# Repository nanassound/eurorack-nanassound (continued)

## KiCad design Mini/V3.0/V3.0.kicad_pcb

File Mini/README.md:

# Mini: USB-C Power Supply

A small and portable USB-C power supply for Eurorack modules.

- It takes 5V input from USB-C port and outputs dual supply +/- 12V and 5V.
- The main component that converts the voltage is [Mean Well DKM10E-12](https://www.meanwell-web.com/en-gb/dc-dc-converter-pcb-mount-input-4-7-9vdc-dual-dkm10e--12).
- The output current according to DKM10E-12 datasheet is ±0 ~ 416mA.
- The input voltage range is 4.7V ~ 9V.

## Design decisions and changes log

#### Version 3

- Make the PCB dimension smaller. There's no point to mount it on the rail and wasting hit point.
- Reduce the amount of power header to 2 headers only.
- Add some capacitors to avoid noise.
- Add a switch to on/off the power supply without unplugging the cable.

#### Version 2

- Make the PCB dimension to fit 3U height and 6HP width, so it can be mounted on a 3U rack.
- Replace 10 pin power header with 16 pin power header and pass 5V from USB-C to the module.
- Replace the glass fuse with 4A PPTC (resettable fuse) to protect the circuit from over current.
- Use SMT components as much as possible to make the layout cleaner.

#### Version 1

- To allow Mini to use 10 pin power header and keep the design small, it **does not** pass 5V. If the Eurorack module requires 5V, then it's the responsibility of the module to provide it by converting the voltage.
- I add 4A fuse as a safety measure.

## Tested USB-C sources

- MacBook Pro [70W USB-C power adapter](https://www.apple.com/shop/product/MXN53AM/A)
- MacBook Pro M2 USB-C port.
- 40W USB-C phone charger (I don't know the brand)
- Xiaomi 10000mAh USB-A to USB-C power bank

## Tested Eurorack modules

- Nanas Sound Uksed
- Doepfer A-111-6
- Crea8audio Function Junction

## Where to buy Mini?

If you are in Europe, you can buy the fully assembled Mini 2.0 from my store on [Reverb](https://reverb.com/en-ee/item/92160894-nanas-sound-mini-usb-c-power-supply).

For the customer outside of Europe, you can buy it from a shared project on [PCBWay](https://www.pcbway.com/project/shareproject/Mini_Eurorack_modular_synth_USB_C_power_supply_29aeece2.html) or [Elecrow](https://www.elecrow.com/sharepj/mini-eurorack-modular-synth-usb-c-power-supply-988.html).

## Photos from the test of Mini version 1

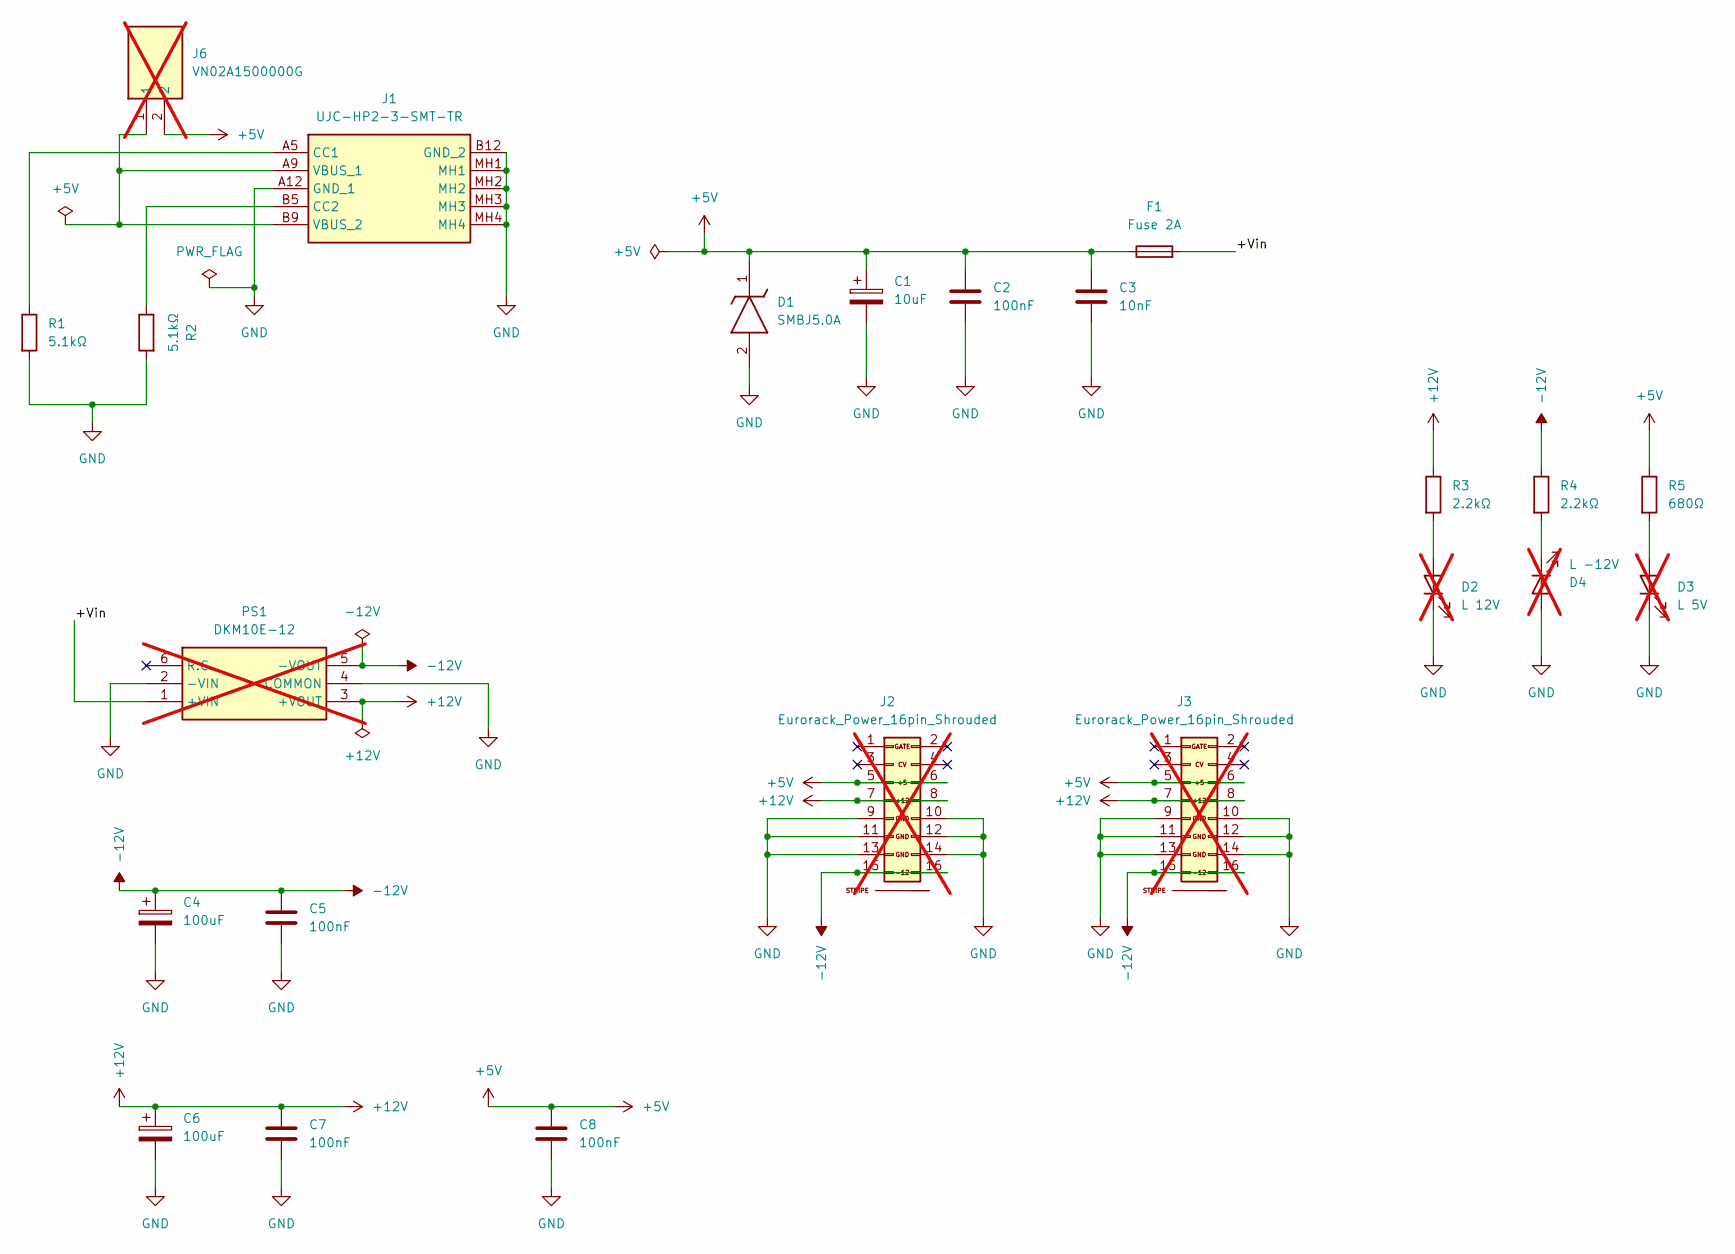
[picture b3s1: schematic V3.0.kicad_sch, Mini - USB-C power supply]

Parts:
C1: 10uF; CP_Elec_6.3x7.7; LCSC Part Number C72482
C2, C5, C7, C8: 100nF; C_0603_1608Metric; LCSC Part Number C14663
C3: 10nF; C_0603_1608Metric; LCSC Part Number C100042
C4, C6: 100uF; CP_Elec_6.3x7.7; LCSC Part Number C48587228
D1: SMBJ5.0A; DIOM5436X244N; Mouser Part Number 652-SMBJ5.0A
D2: L 12V; LED_D2.0mm_W4.8mm_H2.5mm_FlatTop; LCSC Part Number C6717903; not fitted
D3: L 5V; LED_D2.0mm_W4.8mm_H2.5mm_FlatTop; LCSC Part Number C6717903; not fitted
D4: L -12V; LED_D2.0mm_W4.8mm_H2.5mm_FlatTop; LCSC Part Number C6717903; not fitted
F1: Fuse 2A; Fuse_1812_4532Metric; LCSC Part Number C135364
J1: UJC-HP2-3-SMT-TR; UJCHP23SMTTR; Mouser Part Number 179-UJC-HP2-3-SMT-TR
J2, J3: Eurorack_Power_16pin_Shrouded; Pins_2x08_2.54mm_TH_EuroPower_Shrouded_reducedsilk; Part Number LL1007-1 (2*8 HITEMP); not fitted
J6: VN02A1500000G; Mouser Part Number 649-VN02A15000J0G; not fitted
PS1: DKM10E-12; DKM10E12; Mouser Part Number 709-DKM10E-12; not fitted
R1, R2: 5.1kΩ; R_1206_3216Metric; LCSC Part Number C26033
R3, R4: 2.2kΩ; R_1206_3216Metric; LCSC Part Number C17948
R5: 680Ω; R_1206_3216Metric; LCSC Part Number C17975

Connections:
+5V: C1.1, C2.1, C3.1, C8.1, D1.1 (K), F1.1, J2.5 (+12V), J2.6, J3.5 (+12V), J3.6, J6.2, R5.1
+12V: C6.1, C7.1, J2.7 (12V), J2.8 (+12V), J3.7 (12V), J3.8 (+12V), PS1.3 (+VOUT), R3.1
-12V: C4.1, C5.1, J2.15 (-12V), J2.16, J3.15 (-12V), J3.16, PS1.5 (-VOUT), R4.1
/+Vin: F1.2, PS1.1 (+VIN)
GND: C1.2, C2.2, C3.2, C4.2, C5.2, C6.2, C7.2, C8.2, D1.2 (A), D2.1 (K), D3.1 (K), D4.2 (A), J1.A12 (GND_1), J1.B12 (GND_2), J1.MH1, J1.MH2, J1.MH3, J1.MH4, J2.9 (GND), J2.10 (GND), J2.11 (GND), J2.12 (GND), J2.13 (-12), J2.14 (-12V), J3.9 (GND), J3.10 (GND), J3.11 (GND), J3.12 (GND), J3.13 (-12), J3.14 (-12V), PS1.2 (-VIN), PS1.4 (COMMON), R1.2, R2.2
unnamed: D2.2 (A), R3.2
unnamed: D3.2 (A), R5.2
unnamed: D4.1 (K), R4.2
unnamed: J1.A5 (CC1), R1.1
unnamed: J1.B5 (CC2), R2.1
unnamed: J1.A9 (VBUS_1), J1.B9 (VBUS_2), J6.1

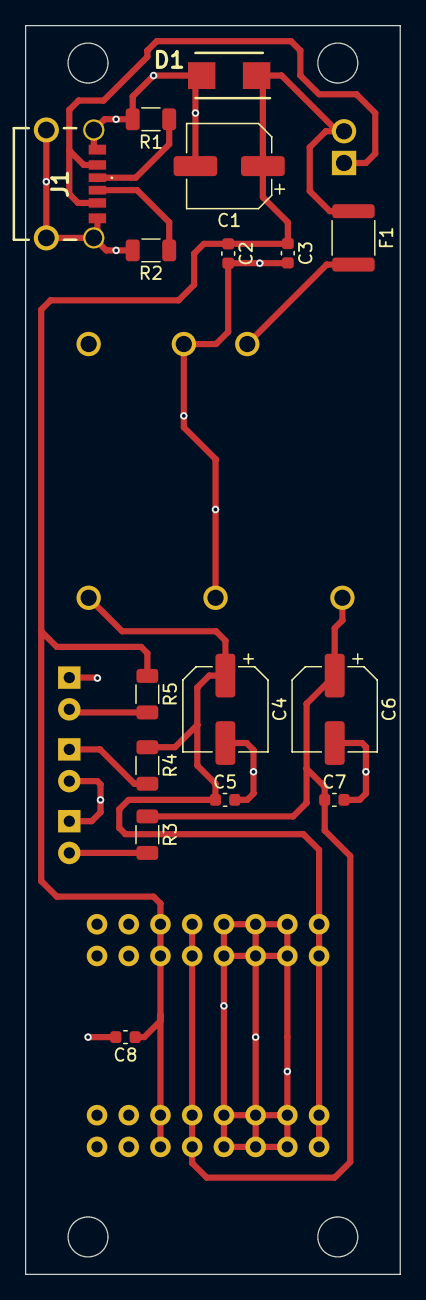
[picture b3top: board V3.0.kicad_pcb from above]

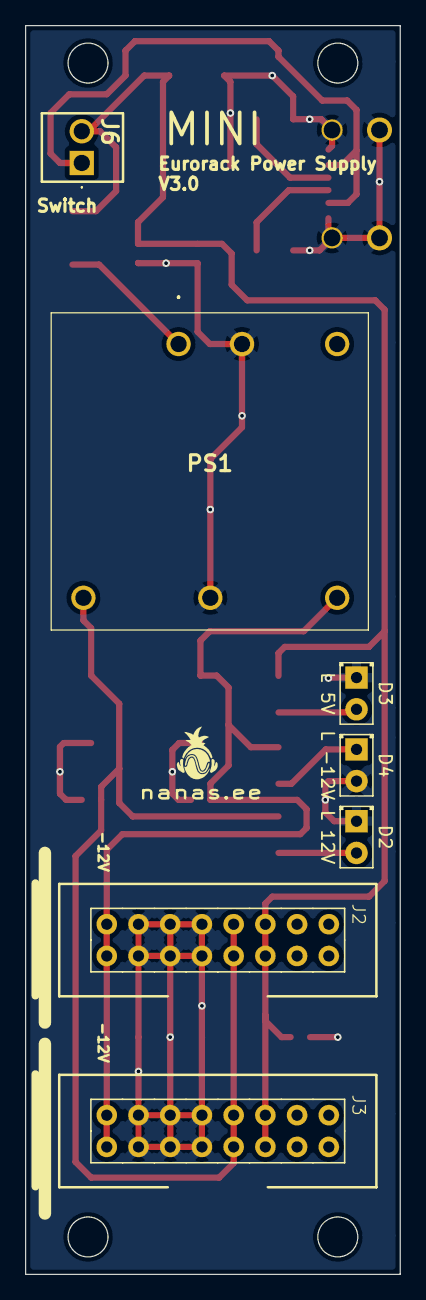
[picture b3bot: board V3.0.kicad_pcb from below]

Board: 2 copper layers, 30.0 x 100.0 mm, 23 parts (7 on the bottom side), 11 nets.

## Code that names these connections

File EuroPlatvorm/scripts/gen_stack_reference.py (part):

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Frames
------
Platform KiCad frame (front view):  x right, y down.
J3 at (137.22, 71.5) LEFT  (power + GPIO0-7 + USB), pins 1..14 running DOWN.
J4 at (149.9,  71.5) RIGHT (GPIO23..8),               pins 1..14 running DOWN.
Headers are THT on the platform BACK (B.Cu) -> a daughter board stacks
back-to-back.  The daughter's KiCad front view equals the platform seen
from behind, i.e. mirrored about the vertical axis, y preserved:
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
# ---------------------------------------------------------------- ground truth
# Platform J3/J4 pinout, taken from the PCB pad net assignments.
J3_NETS = ["+3V3", "+12V", "-12V", "GPIO0", "GPIO1", "GPIO2", "GPIO3",
           "GPIO4", "GPIO5", "GPIO6", "GPIO7", "USB_DP", "USB_DM", "GND"]
J4_NETS = ["GPIO23", "GPIO22", "GPIO21", "GPIO20", "GPIO19", "GPIO18",
           "GPIO17", "GPIO16", "GPIO15", "GPIO11", "GPIO10", "GPIO9",
           "GPIO8", "GND"]

J3_POS = (137.22, 71.5)   # footprint origin, 180 deg, B.Cu
J4_POS = (149.9, 71.5)
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             '\t(layer "F.Cu")\n'
             '\t(descr "EuroPlatvorm carrier stack reference for I/O daughter boards. '
             'Mating field for the two platform back-side 1x14 2.54mm headers: right bank = platform J3 '
             '(+3V3, +12V, -12V, GPIO0-7, USB_DP/DM, GND), left bank = platform J4 (GPIO23-8, GND). '
             'Row spacing 12.68mm (matches platform exactly). Platform outline (21.7x89.75mm) shown on '
             'Dwgs.User; stack back-to-back, daughter B.Cu facing platform B.Cu.")\n'
             '\t(tags "eurorack platvorm europlatvorm carrier daughter shield stack reference esp32-c6")\n')
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    o.append(prop("Datasheet", "", 0, 0, hide=True))
    o.append(prop("Description",
                  "EuroPlatvorm carrier stack reference (ESP32-C6 eurorack platform). "
                  "Place on I/O daughter boards. Right bank = platform J3: +3V3/+12V/-12V, GPIO0-7, "
                  "USB_DP/USB_DM (native USB), GND. Left bank = platform J4: GPIO23..GPIO8, GND. "
                  "GPIO8/GPIO9 are boot strapping pins. Mates with 2x 1x14 2.54mm sockets, "
                  "12.68mm row spacing, platform back-to-back behind the daughter board.", 0, 0, hide=True))
    o.append(prop("ki_keywords", "eurorack platvorm europlatvorm carrier daughter shield esp32-c6", 0, 0, hide=True))
    o.append(prop("ki_fp_filters", "platvorm_custom:EuroPlatvorm*", 0, 0, hide=True))
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
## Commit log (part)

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2024-09-07 Publishing the schematic
2024-09-07 Fixing the link
2024-09-07 Changing the readme
2024-09-08 Adding oscilloscope reading
2024-09-09 Adding online store link
2024-09-12 Add pico-extras as a submodule
2024-09-13 Setup I2C display and I2S DAC
2024-09-17 Make I2S works.
2024-09-18 Integrating Faust with Pico C++
2024-09-30 Setup FreeRTOS
2024-09-30 Add Mini 2.0
2024-09-30 Adding 5V Mini information
2024-09-30 Change the order of the information
2024-10-15 Change the photo
2024-10-19 Add basic things for the lcd menu.
2024-10-20 Handle the rotary encoder event.
2024-11-01 Adding Mini v2 photos
2025-05-12 Add pick and place file for Mini
2025-08-29 Add Uksed to the repository
2025-08-29 Add shop link for Mini.
2026-04-19 Add Mini V3.0 KiCad project and fix .gitignore for KiCad
    Add schematic, PCB layout, fabrication Gerbers, drill files, pick-and-place
    files, and testing guide for Mini V3.0. Update .gitignore to exclude KiCad
    caches, backup directories, autosave files, lock files, and editor history.
2026-04-19 Adding PDF schematic
2026-04-19 Add Mini V3.0 KiCad project and fix .gitignore for KiCad (#1)
    * Add Mini V3.0 KiCad project and fix .gitignore for KiCad
    Add schematic, PCB layout, fabrication Gerbers, drill files, pick-and-place
    files, and testing guide for Mini V3.0. Update .gitignore to exclude KiCad
    caches, backup directories, autosave files, lock files, and editor history.
    * Adding PDF schematic
2026-04-19 Change readme
